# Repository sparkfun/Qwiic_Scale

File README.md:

SparkFun Qwiic Scale
========================================

[*SparkFun Qwiic Scale (SEN-15242)*](https://www.sparkfun.com/products/15242)

This repo is the hardware repo for the Qwiic Scale.

Strain gauges are a lot of fun to play with but they often need complex conditioning and conversion ICs. Qwiic Scale takes care of all the hardware and software concerns and gets you measuring weight!

We've written an extensive Arduino library to make reading a load cell over I2C a breeze. Calibrate, get weight, and you're set.

This board is one of our many [Qwiic](https://www.sparkfun.com/qwiic) compatible boards! Simply plug and go. No soldering, no figuring out which is SDA or SCL, and no voltage regulation or translation required!

SparkFun labored with love to create this code. Feel like supporting open source hardware? 
Buy a [breakout board](https://www.sparkfun.com/products/15242) from SparkFun!

Repository Contents
-------------------

* **/Documents** - Datasheets
* **/Hardware** - Eagle design files (.brd, .sch)

Documentation
--------------
* **[Qwiic Scale Hookup Guide](https://learn.sparkfun.com/tutorials/qwiic-scale-hookup-guide)** - Hookup guide for the Qwiic Scale
* **[Installing an Arduino Library Guide](https://learn.sparkfun.com/tutorials/installing-an-arduino-library)** - Basic information on how to install an Arduino library.
* **[Arduino Library](https://github.com/sparkfun/SparkFun_Qwiic_Scale_NAU7802_Arduino_Library)**

License Information
-------------------

This product is _**open source**_! 

If you have any questions or concerns on licensing, please contact techsupport@sparkfun.com.

Please use, reuse, and modify these files as you see fit. Please maintain attribution to SparkFun Electronics and release any derivative under the same license.

Distributed as-is; no warranty is given.

- Your friends at SparkFun.

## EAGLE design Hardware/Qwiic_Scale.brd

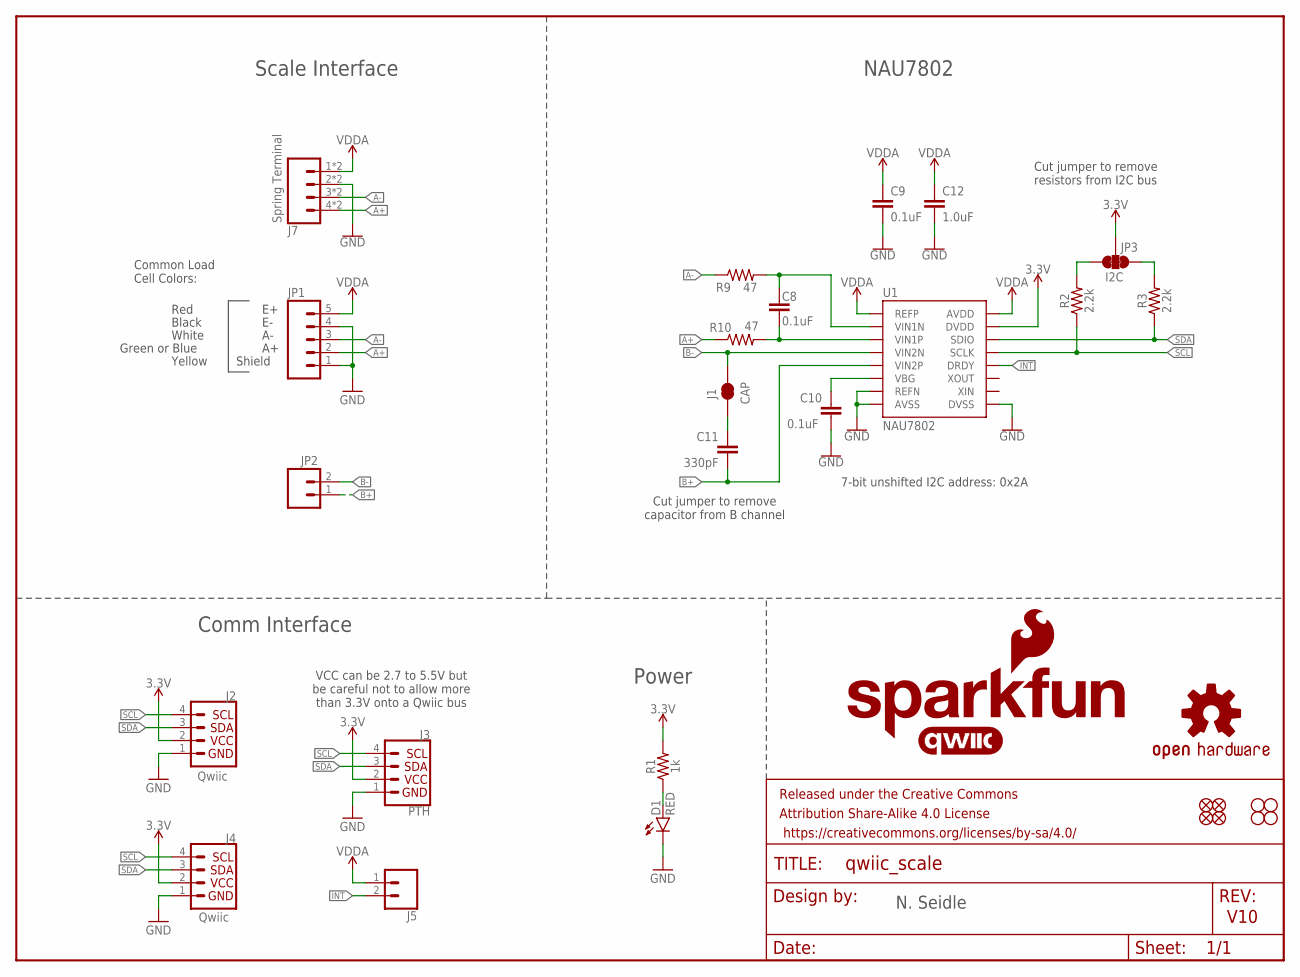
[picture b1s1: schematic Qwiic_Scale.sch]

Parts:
C8, C9, C10: 0.1uF; 0603
C11: 330pF; 0603
C12: 1.0uF; 0603
D1: RED; LED-0603
FRAME1: FRAME-LETTER; CREATIVE_COMMONS
J1: CAP; SMT-JUMPER_2_NC_TRACE_SILK
J2, J4: Qwiic; JST04_1MM_RA
J3: PTH; 1X04_NO_SILK
J5: CONN_021X02_NO_SILK; 1X02_NO_SILK
J7: Spring Terminal; 1X04_SPRING_TERMINAL
JP1: CONN_05NO_SILK; 1X05_NO_SILK
JP2: CONN_021X02_NO_SILK; 1X02_NO_SILK
JP3: I2C; SMT-JUMPER_3_2-NC_TRACE_SILK
JP21, JP61, JP71, JP81: FIDUCIALUFIDUCIAL; MICRO-FIDUCIAL
JP31, JP41, JP91, JP101: STAND-OFF
LOGO1: OSHW-LOGOMINI; OSHW-LOGO-MINI
LOGO2: SFE_LOGO_NAME_FLAME.1_INCH; SFE_LOGO_NAME_FLAME_.1
R1: 1k; 0603
R2, R3: 2.2k; 0603
R9, R10: 47; 0603
U1: NAU7802; SO16
U$16: QWIIC_LOGO_7MM; QWIIC_7MM

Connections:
3.3V: J2.2, J3.2, J4.2, JP3.2, R1.2, U1.15 (DVDD)
A+: J7.4, J7.8 (4), JP1.2, R10.1
A-: J7.3, J7.7 (3), JP1.3, R9.1
B+: C11.2, JP2.1, U1.5 (VIN2P)
B-: J1.2, JP2.2, U1.4 (VIN2N)
GND: C9.2, C10.2, C12.2, D1.C, J2.1, J3.1, J4.1, J7.2, J7.6 (2), JP1.1, JP1.4, U1.7 (REFN), U1.8 (AVSS), U1.9 (DVSS)
INT: J5.2, U1.12 (DRDY)
unnamed: C11.1, J1.1
unnamed: JP3.1, R3.2
unnamed: JP3.3, R2.2
unnamed: D1.A, R1.1
unnamed: C10.1, U1.6 (VBG)
unnamed: C8.2, R10.2, U1.3 (VIN1P)
unnamed: C8.1, R9.2, U1.2 (VIN1N)
SCL: J2.4, J3.4, J4.4, R2.1, U1.13 (SCLK)
SDA: J2.3, J3.3, J4.3, R3.1, U1.14 (SDIO)
VDDA: C9.1, C12.1, J5.1, J7.1, J7.5 (1), JP1.5, U1.1 (REFP), U1.16 (AVDD)

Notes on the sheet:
V10
7-bit unshifted I2C address: 0x2A
Cut jumper to remove resistors from I2C bus
Red
Black
White
Green or Blue
Common Load Cell Colors:
Shield
Yellow
Cut jumper to remove capacitor from B channel
N. Seidle
NAU7802
Comm Interface
Scale Interface
Power
VCC can be 2.7 to 5.5V but be careful not to allow more than 3.3V onto a Qwiic bus

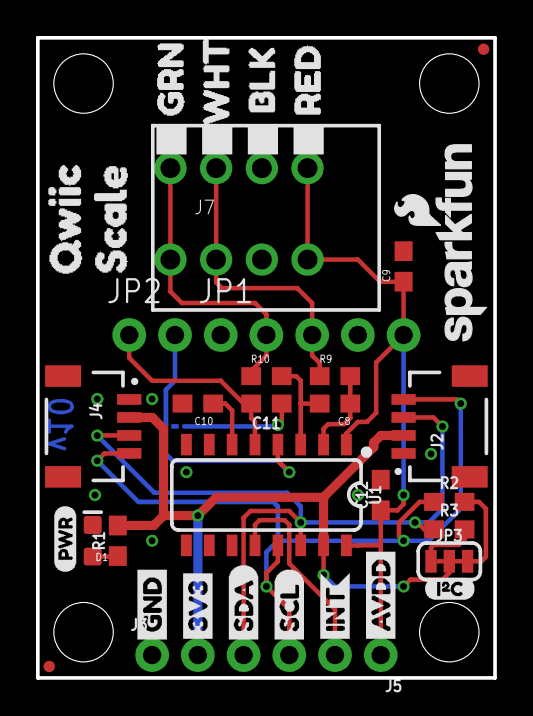
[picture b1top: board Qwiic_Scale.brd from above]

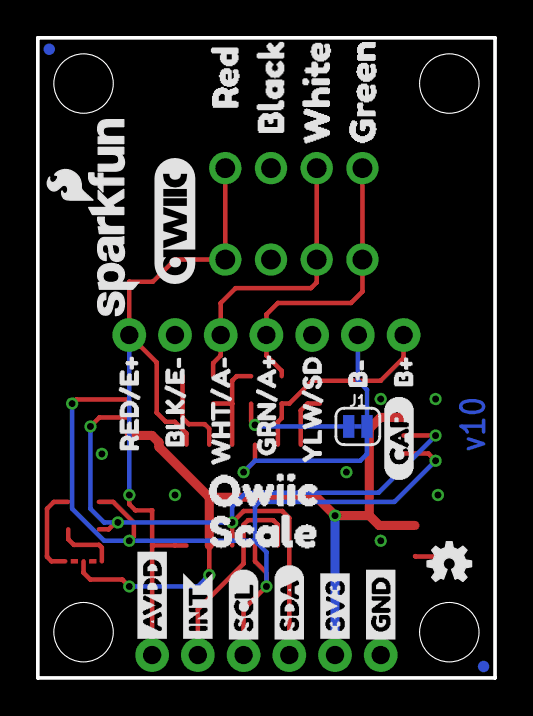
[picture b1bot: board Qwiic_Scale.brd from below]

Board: 2 copper layers, 25.4 x 35.6 mm, 68 parts (26 on the bottom side), 17 nets.

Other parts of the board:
LOGO3: SFE_LOGO_NAME_FLAME.1_INCH; SFE_LOGO_NAME_FLAME_.1
U$1, U$4: SDA-[)
U$3, U$5: SCL-[)
U$6, U$7: 3V3-04
U$8, U$9: GND-04
U$11: YLW#SD4
U$12: B#11
U$13: B#12
U$14, U$22: QWIIC2
U$15, U$21: INT0
U$17, U$24: SCALE3
U$18: PWR-()-03
U$19: I_SUPER2_C-()-03
U$20: CAP0
U$34: BLK#E#1
U$35: GRN#A#4
U$36, U$45: AVDD4
U$37: BLACK5
U$38: BLK1
U$39: GREEN7
U$40: GRN3
U$41: RED0
U$42: RED4
U$43: WHITE6
U$44: WHT2
U$46: RED#E#2
U$48: WHT#A#3

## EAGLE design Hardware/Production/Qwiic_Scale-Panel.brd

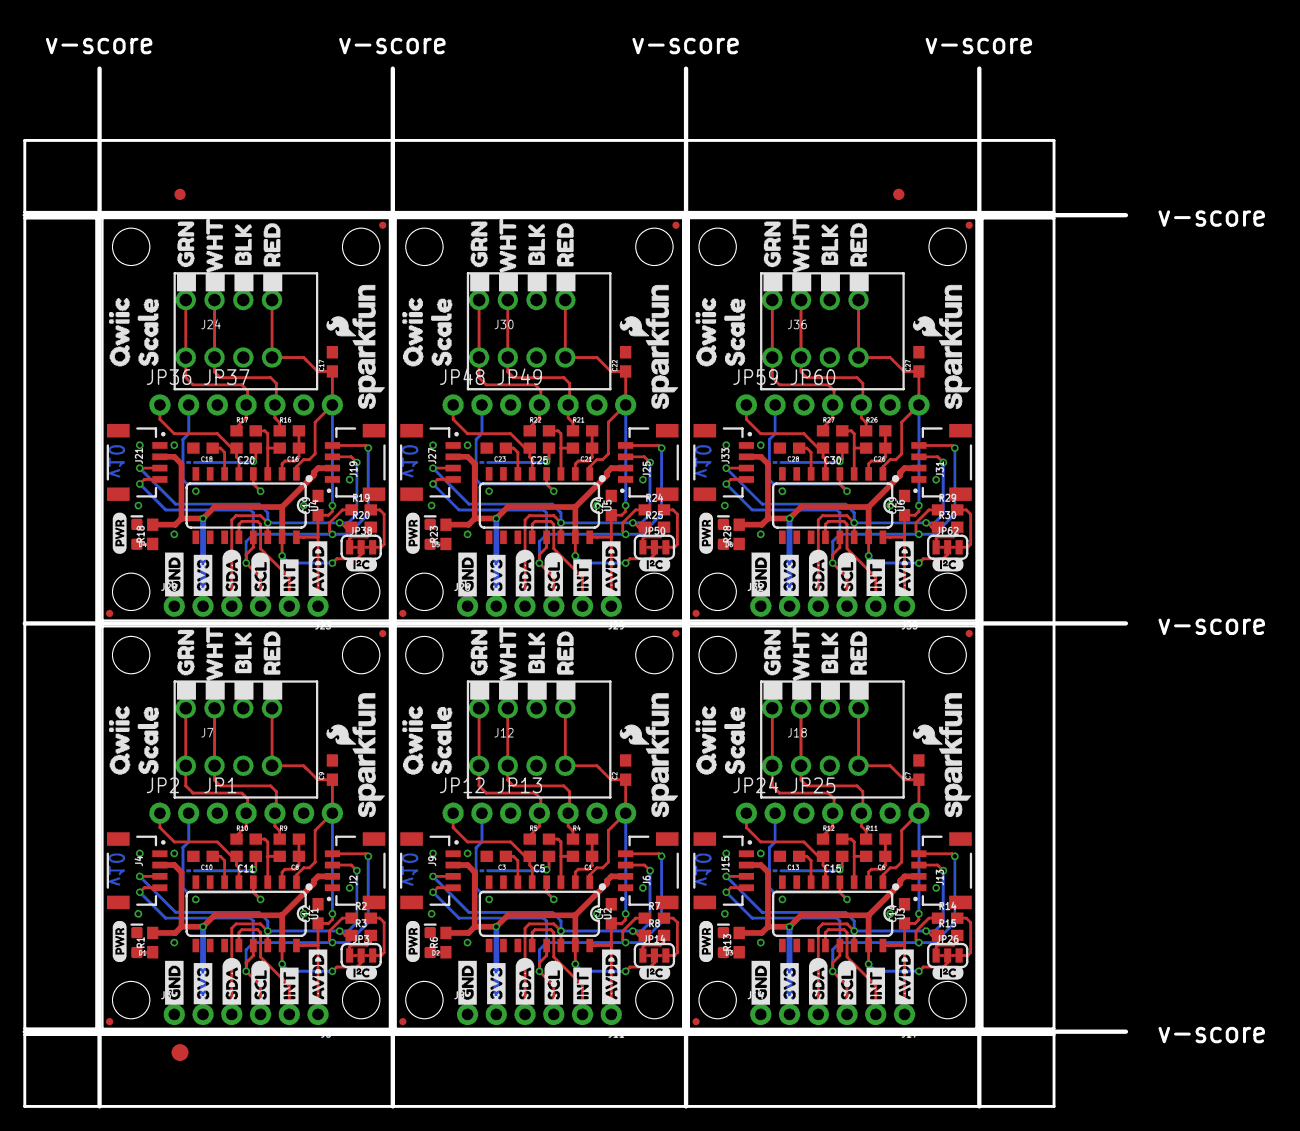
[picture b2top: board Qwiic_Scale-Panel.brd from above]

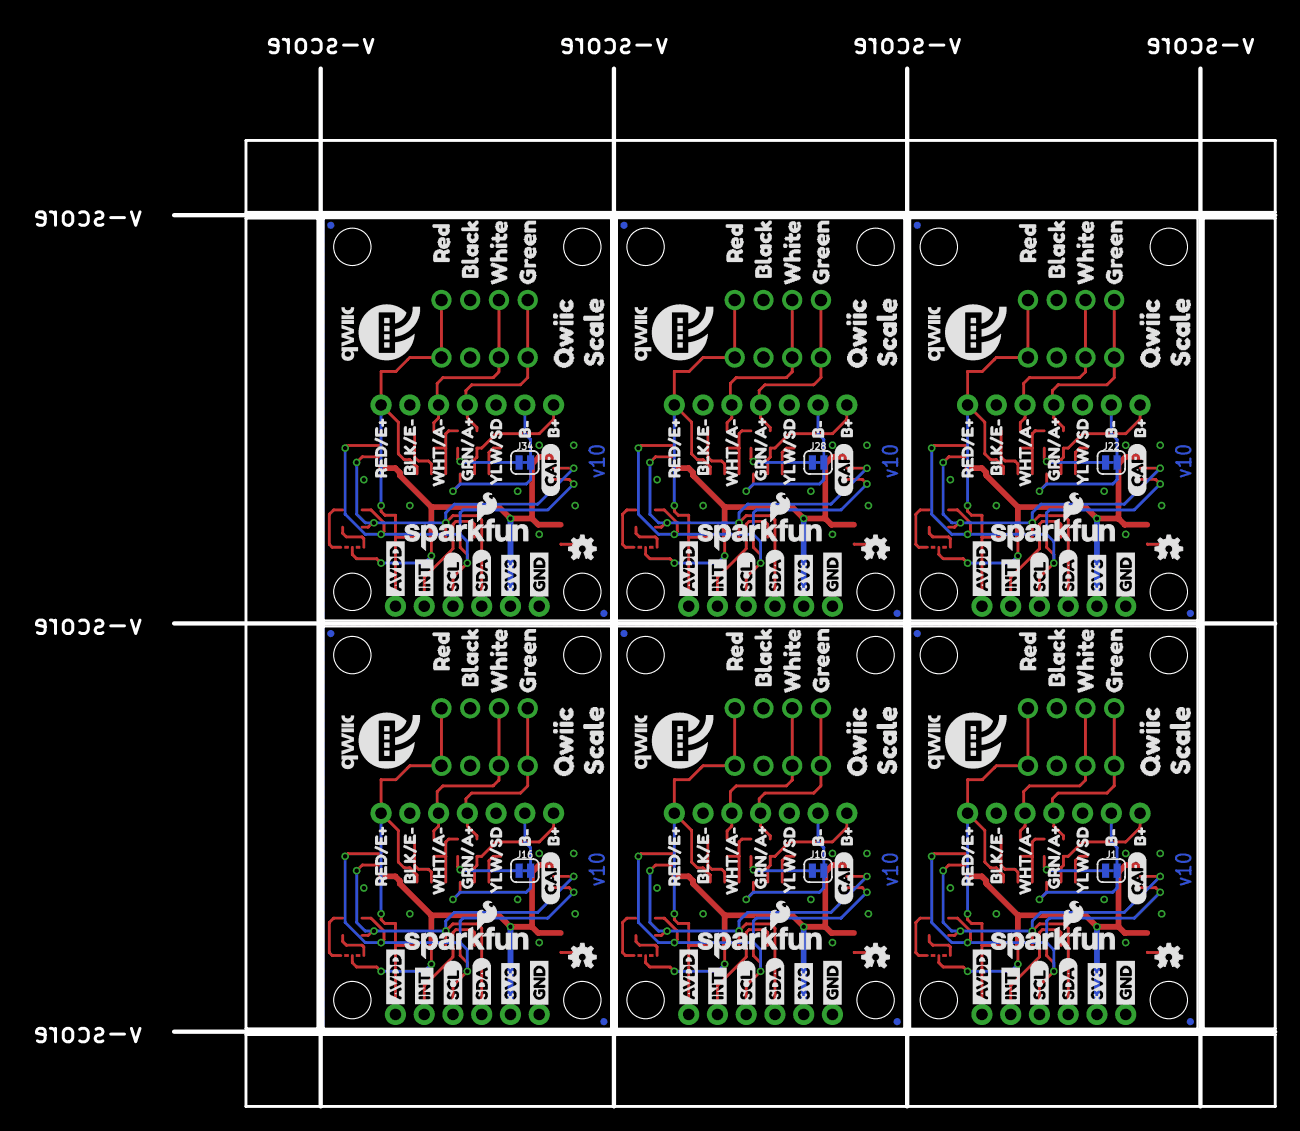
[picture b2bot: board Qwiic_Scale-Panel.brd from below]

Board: 2 copper layers, 97.3 x 91.7 mm, 405 parts (156 on the bottom side), 102 nets.

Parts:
C1, C2, C3, C6, C7, C8, C9, C10, C13, C16, C17, C18, C21, C22, C23, C26, C27, C28: 0.1uF; 0603
C4, C12, C14, C19, C24, C29: 1.0uF; 0603
C5, C11, C15, C20, C25, C30: 330pF; 0603
D1, D2, D3, D4, D5, D6: RED; LED-0603
E$1, E$2: FIDUCIAL-1X2
E$3: FIDUCIAL-1.5X3
J1, J10, J16, J22, J28, J34: CAP; SMT-JUMPER_2_NC_TRACE_SILK
J2, J4, J6, J9, J13, J15, J19, J21, J25, J27, J31, J33: Qwiic Right Angle; JST04_1MM_RA
J3, J8, J14, J20, J26, J32: PTH; 1X04_NO_SILK
J5, J11, J17, J23, J29, J35: 1X02_NO_SILK
J7, J12, J18, J24, J30, J36: Spring Terminal; 1X04_SPRING_TERMINAL
JP1, JP13, JP25, JP37, JP49, JP60: 1X05_NO_SILK
JP2, JP12, JP24, JP36, JP48, JP59: 1X02_NO_SILK
JP3, JP14, JP26, JP38, JP50, JP62: I2C; SMT-JUMPER_3_2-NC_TRACE_SILK
JP4, JP5, JP10, JP11, JP15, JP16, JP22, JP23, JP27, JP28, JP31, JP34, JP35, JP39, JP40, JP41, JP46, JP47, JP51, JP52, JP57, JP58, JP91, JP101: STAND-OFF
JP6, JP7, JP8, JP9, JP17, JP18, JP19, JP20, JP21, JP29, JP30, JP32, JP33, JP42, JP43, JP44, JP45, JP53, JP54, JP55, JP56, JP61, JP71, JP81: FIDUCIALUFIDUCIAL; MICRO-FIDUCIAL
LOGO1, LOGO4, LOGO7, LOGO10, LOGO13, LOGO16: OSHW-LOGOMINI; OSHW-LOGO-MINI
LOGO2, LOGO3, LOGO5, LOGO6, LOGO8, LOGO9, LOGO11, LOGO12, LOGO14, LOGO15, LOGO17, LOGO18: SFE_LOGO_NAME_FLAME.1_INCH; SFE_LOGO_NAME_FLAME_.1
R1, R6, R13, R18, R23, R28: 1k; 0603
R2, R3, R7, R8, R14, R15, R19, R20, R24, R25, R29, R30: 2.2k; 0603
R4, R5, R9, R10, R11, R12, R16, R17, R21, R22, R26, R27: 47; 0603
U1, U2, U3, U4, U5, U6: NAU7802; SO16
U$1, U$2, U$4, U$14, U$71, U$73, U$106, U$108, U$141, U$143, U$176, U$178: SDA-[)
U$3, U$5, U$10, U$21, U$72, U$74, U$107, U$109, U$142, U$144, U$177, U$179: SCL-[)
U$6, U$7, U$23, U$26, U$75, U$76, U$110, U$111, U$145, U$146, U$180, U$181: 3V3-04
U$8, U$9, U$27, U$28, U$77, U$78, U$112, U$113, U$147, U$148, U$182, U$183: GND-04
U$11, U$62, U$97, U$132, U$167, U$202: YLW#SD4
U$12, U$47, U$83, U$118, U$153, U$188: B#11
U$13, U$49, U$84, U$119, U$154, U$189: B#12
U$15, U$16, U$29, U$31, U$79, U$80, U$114, U$115, U$149, U$150, U$184, U$185: INT8
U$17, U$22, U$65, U$67, U$100, U$102, U$135, U$137, U$170, U$172, U$205, U$207: QWIIC2
U$18, U$33, U$82, U$117, U$152, U$187: PWR-()-03
U$19, U$69, U$104, U$139, U$174, U$209: I_SUPER2_C-()-03
U$20, U$70, U$105, U$140, U$175, U$210: CAP0
U$24, U$25, U$66, U$68, U$101, U$103, U$136, U$138, U$171, U$173, U$206, U$208: SCALE3
U$30, U$32, U$81, U$116, U$151, U$186: QWIIC-LOGO-MEDIUM
U$34, U$58, U$93, U$128, U$163, U$198: BLK#E#1
U$35, U$59, U$94, U$129, U$164, U$199: GRN#A#4
U$36, U$45, U$63, U$64, U$98, U$99, U$133, U$134, U$168, U$169, U$203, U$204: AVDD4
U$37, U$50, U$85, U$120, U$155, U$190: BLACK5
U$38, U$51, U$86, U$121, U$156, U$191: BLK1
U$39, U$52, U$87, U$122, U$157, U$192: GREEN7
U$40, U$53, U$88, U$123, U$158, U$193: GRN3
U$41, U$54, U$89, U$124, U$159, U$194: RED0
U$42, U$55, U$90, U$125, U$160, U$195: RED4
U$43, U$56, U$91, U$126, U$161, U$196: WHITE6
U$44, U$57, U$92, U$127, U$162, U$197: WHT2
U$46, U$60, U$95, U$130, U$165, U$200: RED#E#2
U$48, U$61, U$96, U$131, U$166, U$201: WHT#A#3

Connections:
3.3V: J2.2, J3.2, J4.2, JP3.2, R1.2, U1.15
3.3V1: J6.2, J8.2, J9.2, JP14.2, R6.2, U2.15
3.3V2: J13.2, J14.2, J15.2, JP26.2, R13.2, U3.15
3.3V3: J19.2, J20.2, J21.2, JP38.2, R18.2, U4.15
3.3V4: J25.2, J26.2, J27.2, JP50.2, R23.2, U5.15
3.3V5: J31.2, J32.2, J33.2, JP62.2, R28.2, U6.15
A+: J7.4, J7.8, JP1.2, R10.1
A+1: J12.4, J12.8, JP13.2, R5.1
A+2: J18.4, J18.8, JP25.2, R12.1
A+3: J24.4, J24.8, JP37.2, R17.1
A+4: J30.4, J30.8, JP49.2, R22.1
A+5: J36.4, J36.8, JP60.2, R27.1
A-: J7.3, J7.7, JP1.3, R9.1
A-1: J12.3, J12.7, JP13.3, R4.1
A-2: J18.3, J18.7, JP25.3, R11.1
A-3: J24.3, J24.7, JP37.3, R16.1
A-4: J30.3, J30.7, JP49.3, R21.1
A-5: J36.3, J36.7, JP60.3, R26.1
B+: C11.2, JP2.1, U1.5
B+1: C5.2, JP12.1, U2.5
B+2: C15.2, JP24.1, U3.5
B+3: C20.2, JP36.1, U4.5
B+4: C25.2, JP48.1, U5.5
B+5: C30.2, JP59.1, U6.5
B-: J1.2, JP2.2, U1.4
B-1: J10.2, JP12.2, U2.4
B-2: J16.2, JP24.2, U3.4
B-3: J22.2, JP36.2, U4.4
B-4: J28.2, JP48.2, U5.4
B-5: J34.2, JP59.2, U6.4
GND: C9.2, C10.2, C12.2, D1.C, J2.1, J3.1, J4.1, J7.2, J7.6, JP1.1, JP1.4, U1.7, U1.8, U1.9
GND1: C2.2, C3.2, C4.2, D2.C, J6.1, J8.1, J9.1, J12.2, J12.6, JP13.1, JP13.4, U2.7, U2.8, U2.9
GND2: C7.2, C13.2, C14.2, D3.C, J13.1, J14.1, J15.1, J18.2, J18.6, JP25.1, JP25.4, U3.7, U3.8, U3.9
GND3: C17.2, C18.2, C19.2, D4.C, J19.1, J20.1, J21.1, J24.2, J24.6, JP37.1, JP37.4, U4.7, U4.8, U4.9
GND4: C22.2, C23.2, C24.2, D5.C, J25.1, J26.1, J27.1, J30.2, J30.6, JP49.1, JP49.4, U5.7, U5.8, U5.9
GND5: C27.2, C28.2, C29.2, D6.C, J31.1, J32.1, J33.1, J36.2, J36.6, JP60.1, JP60.4, U6.7, U6.8, U6.9
INT: J5.2, U1.12
INT1: J11.2, U2.12
INT2: J17.2, U3.12
INT3: J23.2, U4.12
INT4: J29.2, U5.12
INT5: J35.2, U6.12
unnamed: C11.1, J1.1
unnamed: JP3.1, R3.2
unnamed: JP3.3, R2.2
unnamed: D2.A, R6.1
unnamed: C3.1, U2.6
unnamed: C1.2, R5.2, U2.3
unnamed: C1.1, R4.2, U2.2
unnamed: C5.1, J10.1
unnamed: JP14.1, R8.2
unnamed: D1.A, R1.1
unnamed: C10.1, U1.6
unnamed: JP14.3, R7.2
unnamed: D3.A, R13.1
unnamed: C13.1, U3.6
unnamed: C8.2, R10.2, U1.3
unnamed: C8.1, R9.2, U1.2
unnamed: C6.2, R12.2, U3.3
unnamed: C6.1, R11.2, U3.2
unnamed: C15.1, J16.1
unnamed: JP26.1, R15.2
unnamed: JP26.3, R14.2
unnamed: D4.A, R18.1
unnamed: C18.1, U4.6
unnamed: C16.2, R17.2, U4.3
unnamed: C16.1, R16.2, U4.2
unnamed: C20.1, J22.1
unnamed: JP38.1, R20.2
unnamed: JP38.3, R19.2
unnamed: D5.A, R23.1
unnamed: C23.1, U5.6
unnamed: C21.2, R22.2, U5.3
unnamed: C21.1, R21.2, U5.2
unnamed: C25.1, J28.1
unnamed: JP50.1, R25.2
unnamed: JP50.3, R24.2
unnamed: D6.A, R28.1
unnamed: C28.1, U6.6
unnamed: C26.2, R27.2, U6.3
unnamed: C26.1, R26.2, U6.2
unnamed: C30.1, J34.1
unnamed: JP62.1, R30.2
unnamed: JP62.3, R29.2
SCL: J2.4, J3.4, J4.4, R2.1, U1.13
SCL1: J6.4, J8.4, J9.4, R7.1, U2.13
SCL2: J13.4, J14.4, J15.4, R14.1, U3.13
SCL3: J19.4, J20.4, J21.4, R19.1, U4.13
SCL4: J25.4, J26.4, J27.4, R24.1, U5.13
SCL5: J31.4, J32.4, J33.4, R29.1, U6.13
SDA: J2.3, J3.3, J4.3, R3.1, U1.14
SDA1: J6.3, J8.3, J9.3, R8.1, U2.14
SDA2: J13.3, J14.3, J15.3, R15.1, U3.14
SDA3: J19.3, J20.3, J21.3, R20.1, U4.14
SDA4: J25.3, J26.3, J27.3, R25.1, U5.14
SDA5: J31.3, J32.3, J33.3, R30.1, U6.14
VDDA: C9.1, C12.1, J5.1, J7.1, J7.5, JP1.5, U1.1, U1.16
VDDA1: C2.1, C4.1, J11.1, J12.1, J12.5, JP13.5, U2.1, U2.16
VDDA2: C7.1, C14.1, J17.1, J18.1, J18.5, JP25.5, U3.1, U3.16
VDDA3: C17.1, C19.1, J23.1, J24.1, J24.5, JP37.5, U4.1, U4.16
VDDA4: C22.1, C24.1, J29.1, J30.1, J30.5, JP49.5, U5.1, U5.16
VDDA5: C27.1, C29.1, J35.1, J36.1, J36.5, JP60.5, U6.1, U6.16

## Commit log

2019-02-19 Fixing FP on terminal. Adding ignore.
2019-02-19 Updating spring terminal. Adding prod IDs. Update readme.
2019-02-19 Adding panel
2019-02-20 Silk change to terminal. Better ground ties.
2019-03-04 Remove examples. Add proto panel. Move firmware to library repo.
2019-03-05 Divided schematic. Added VDD range.
2019-03-07 Update Qwiic logo. Remove old panel files.
2019-03-07 Change int flag to output
2019-03-07 Changing int flag to output
2019-04-08 Remove extraneous wire from schematic
2019-04-08 Update image

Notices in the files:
parts and their libraries:
SparkFun-Resistors: Licensing: Creative Commons ShareAlike 4.0 International - https://creativecommons.org/licenses/by-sa/4.0
SparkFun-Aesthetics: Released under the Creative Commons Attribution Share-Alike 4.0 License
SparkFun-Aesthetics: https://creativecommons.org/licenses/by-sa/4.0
